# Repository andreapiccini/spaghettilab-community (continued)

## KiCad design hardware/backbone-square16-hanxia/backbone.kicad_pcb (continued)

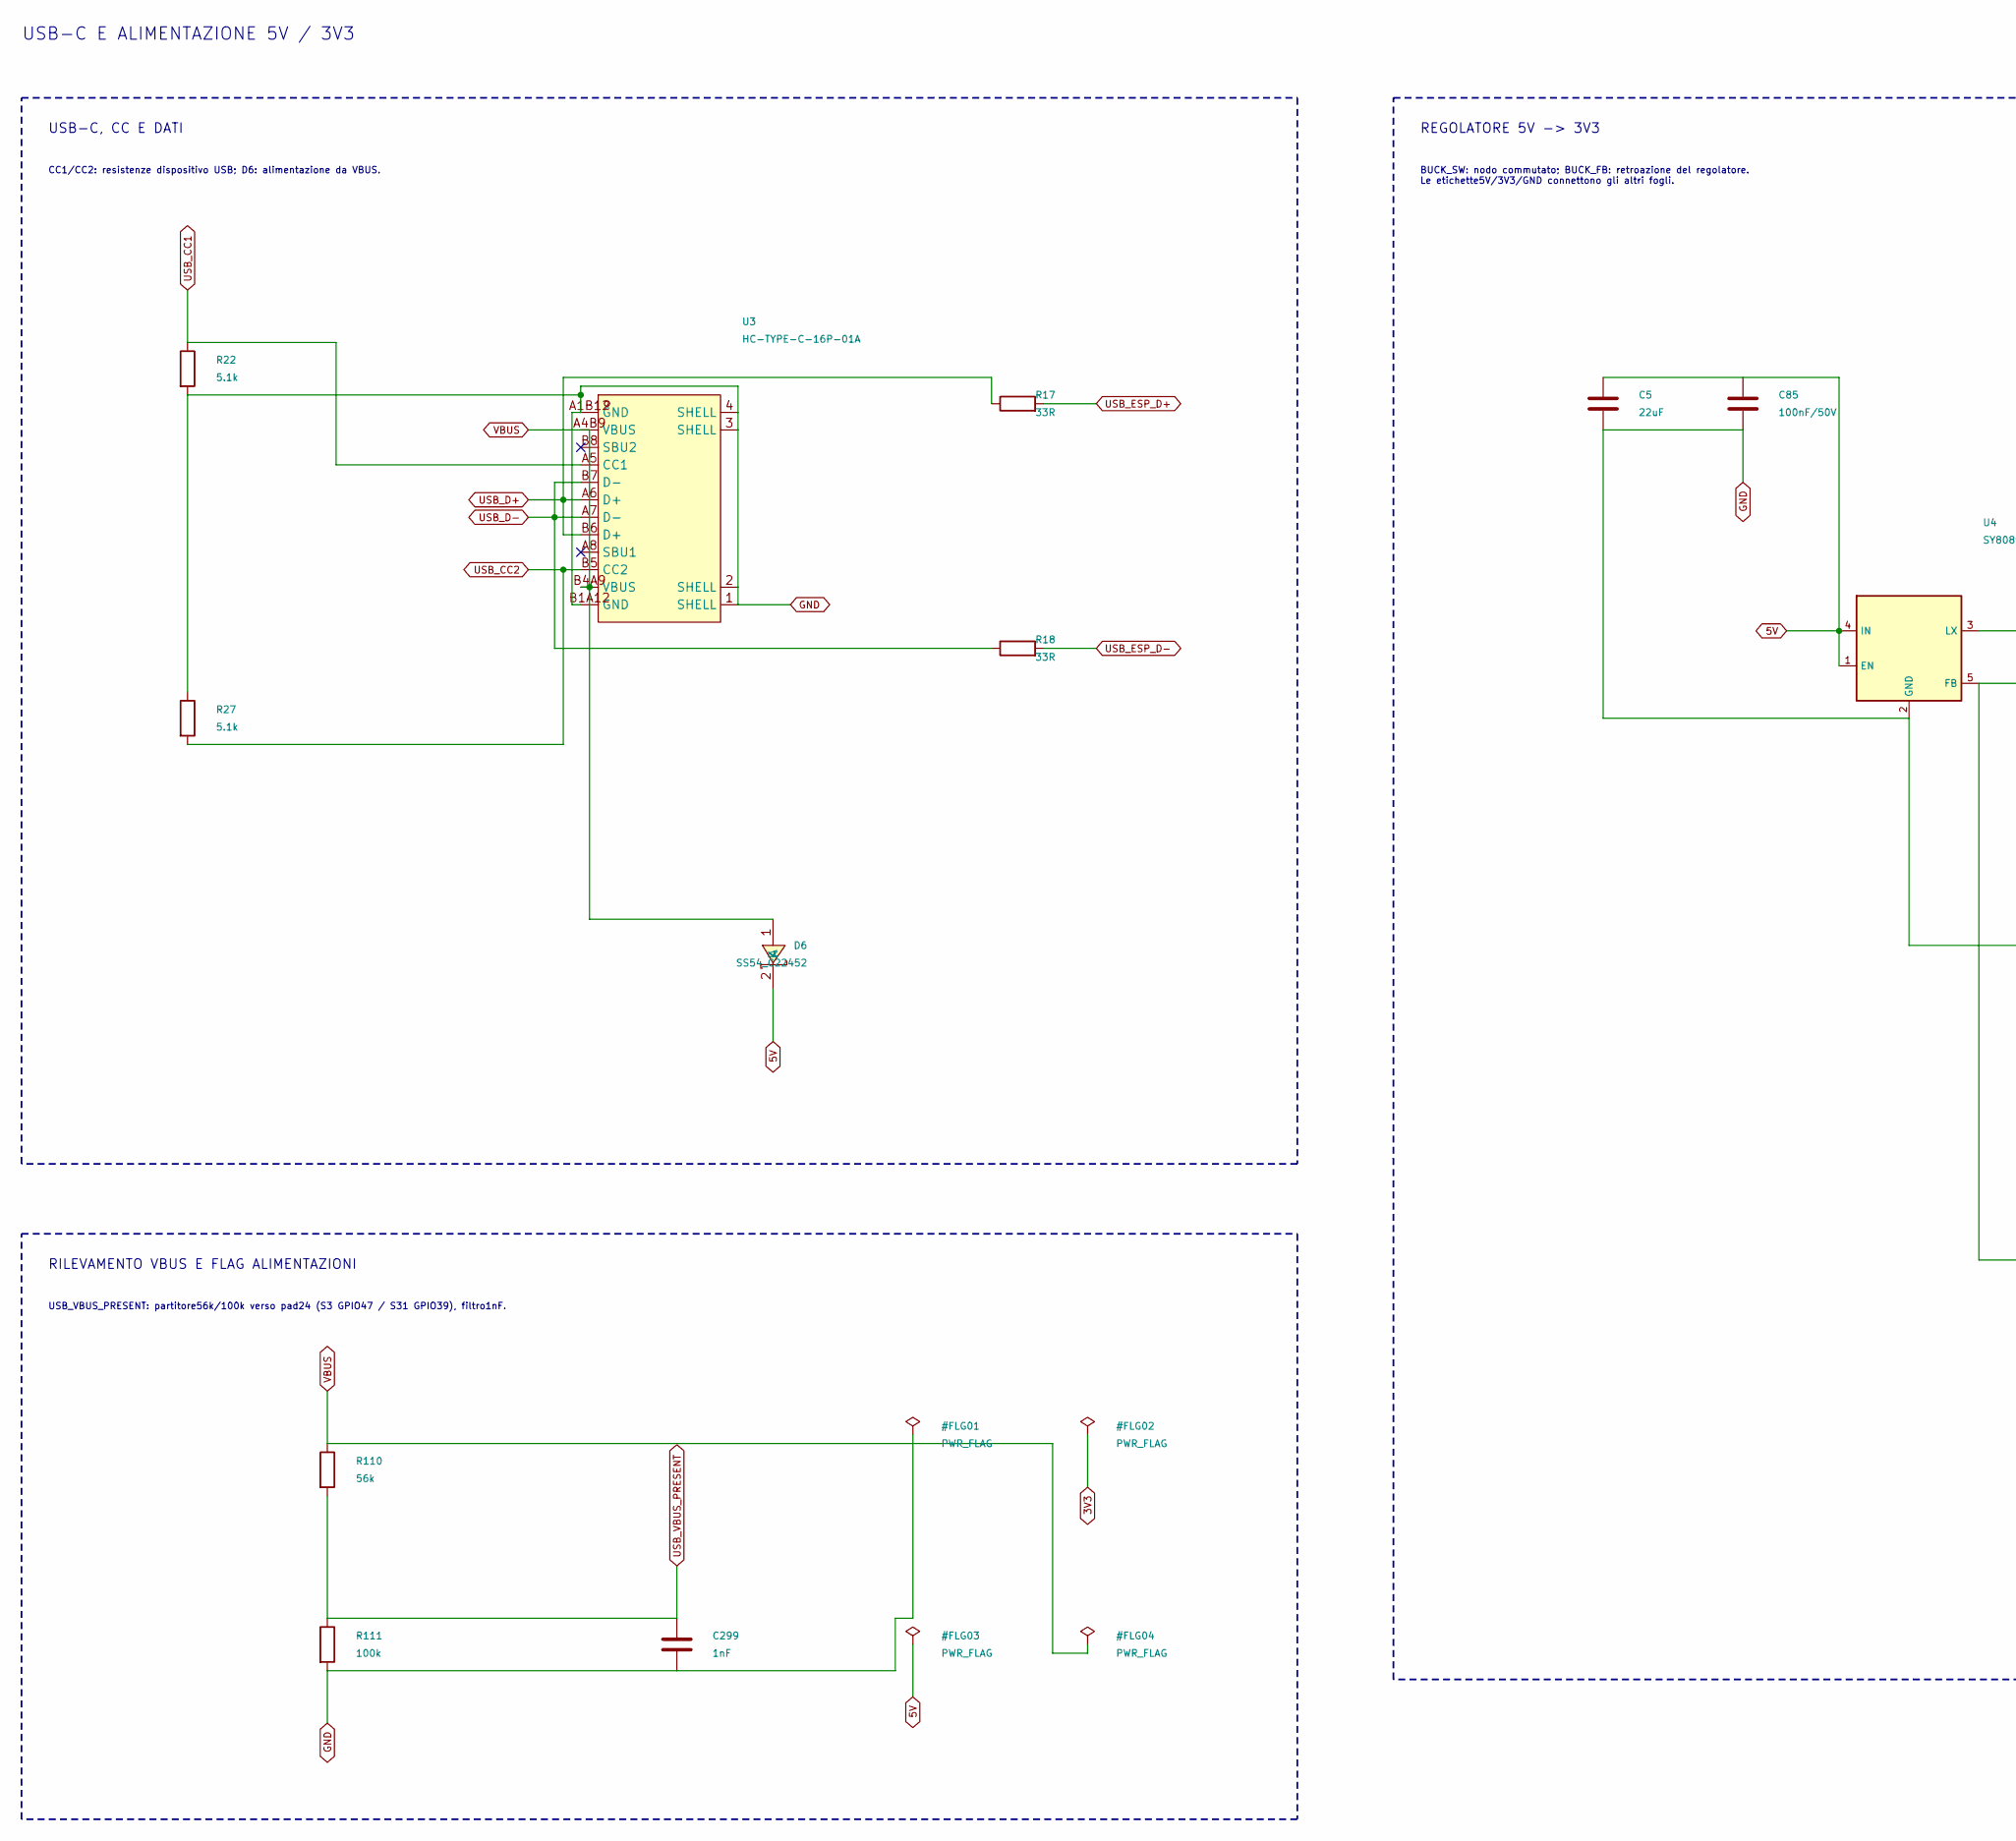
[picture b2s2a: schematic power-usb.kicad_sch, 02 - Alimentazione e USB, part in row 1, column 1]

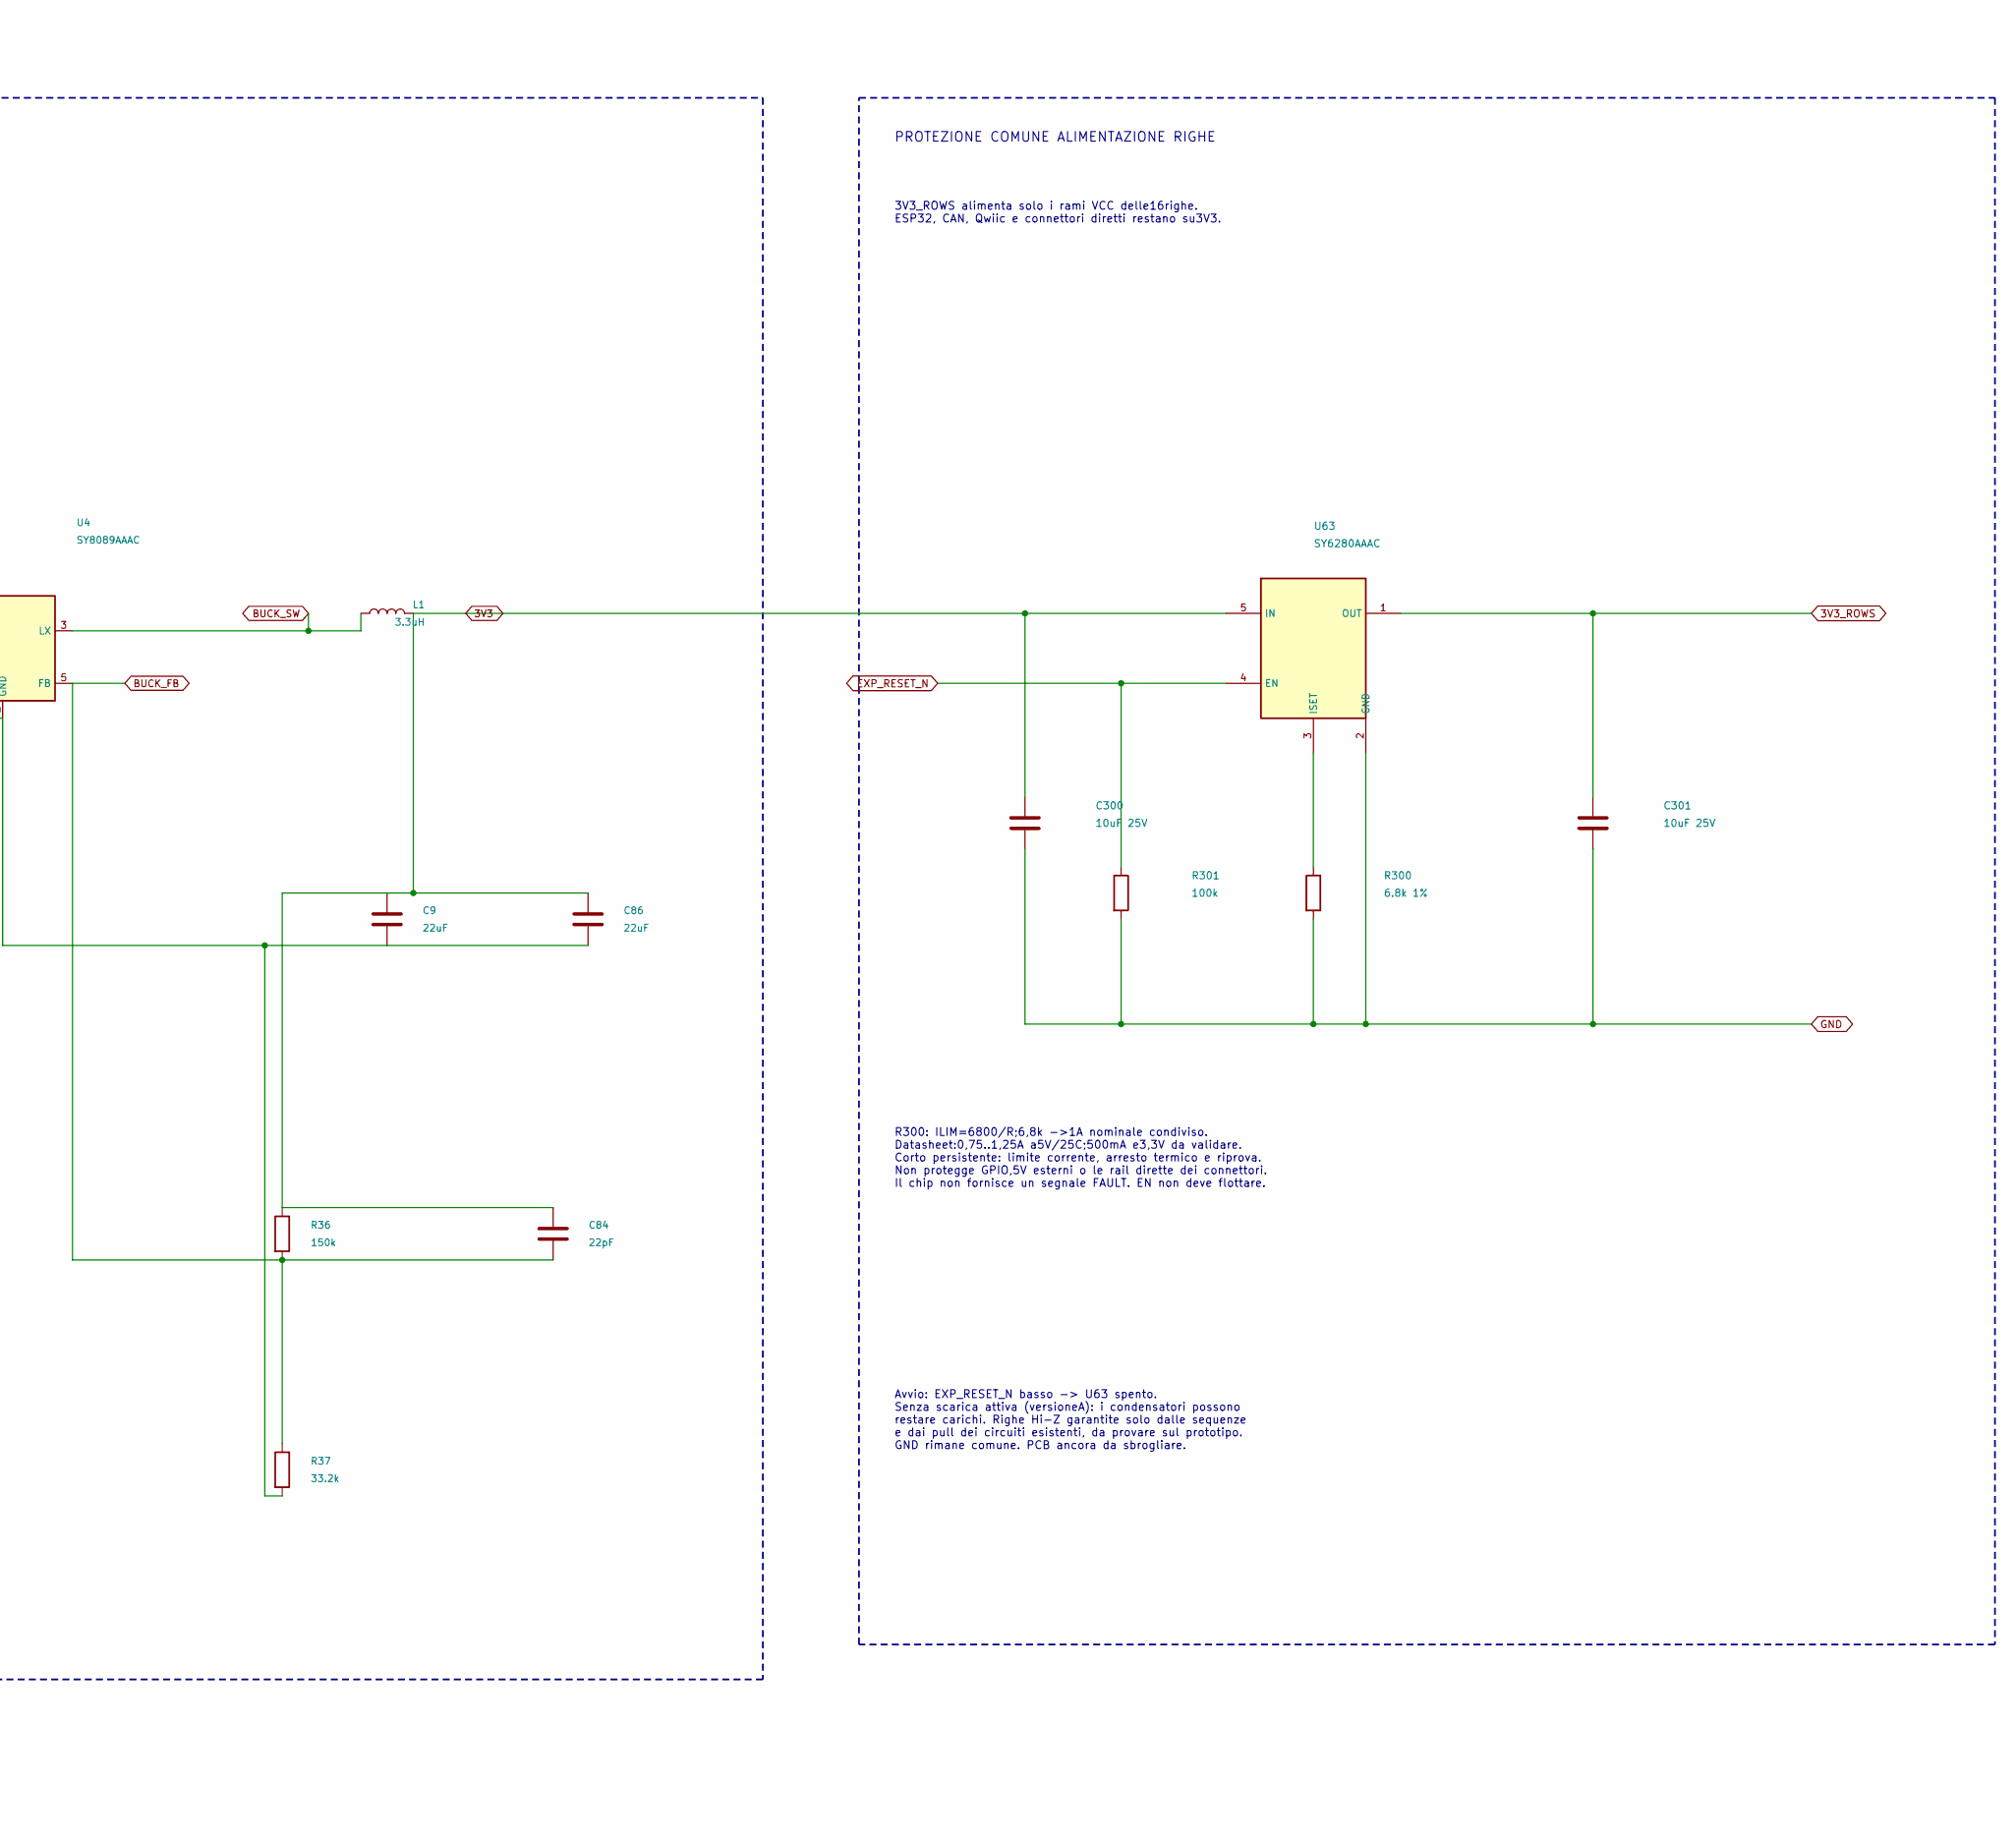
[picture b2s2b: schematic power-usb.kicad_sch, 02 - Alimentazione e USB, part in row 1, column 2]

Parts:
C5, C9, C86: 22uF; C_0603_1608Metric; MPN CL10A226MP8NUNE; LCSC Part C86295
C84: 22pF; C_0603_1608Metric; MPN CL10C220JB8NNNC; LCSC Part C1653
C85: 100nF/50V; C_0603_1608Metric; MPN CL10B104KB8NNNC; LCSC Part C1591
C299: 1nF; C_0603_1608Metric
C300, C301: 10uF 25V; C_0805_2012Metric; MPN CL21A106KAYNNNE; LCSC Part C15850
D6: SS54_C22452; SMA_L4.4-W2.8-LS5.4-R-RD; MPN SS54; LCSC Part C22452
L1: 3.3uH; L_XRTC404012S; MPN XRTC404012S3R3MBCA; LCSC Part C39846848
R17, R18: 33R; R0603; LCSC Part C2909394
R22, R27: 5.1k; R0603; LCSC Part C2907044
R36: 150k; R_0603_1608Metric; MPN 0603WAF1503T5E; LCSC Part C22807
R37: 33.2k; R_0603_1608Metric; MPN 0603WAF3322T5E; LCSC Part C23003
R110: 56k; R_0603_1608Metric
R111: 100k; R_0603_1608Metric
R300: 6.8k 1%; R_0603_1608Metric; MPN 0603WAF6801T5E; LCSC Part C23212
R301: 100k; R_0603_1608Metric; MPN 0603WAF1003T5E; LCSC Part C25803
U3: HC-TYPE-C-16P-01A; USB-C-SMD_HC-TYPE-C-16P-01A_ClearSilk; MPN HC-TYPE-C-16P-01A; LCSC Part C2894897
U4: SY8089AAAC; SOT-23-5; MPN SY8089AAAC; LCSC Part C78988
U63: SY6280AAAC; SOT-23-5; MPN SY6280AAAC; LCSC Part C207620

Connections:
3V3: C9.1, C84.1, C86.1, C300.1, L1.2, R36.1, U63.5 (IN); also elsewhere on the board
3V3_ROWS: C301.1, U63.1 (OUT); also elsewhere on the board
5V: C5.1, C85.1, D6.2 (K), U4.1 (EN), U4.4 (IN); also elsewhere on the board
BUCK_FB: C84.2, R36.2, R37.1, U4.5 (FB)
BUCK_SW: L1.1, U4.3 (LX)
EXP_RESET_N: R301.1, U63.4 (EN); also elsewhere on the board
GND: C5.2, C9.2, C85.2, C86.2, C299.2, C300.2, C301.2, R22.2, R27.1, R37.2, R111.2, R300.2, R301.2, U3.1 (SHELL), U3.2 (SHELL), U3.3 (SHELL), U3.4 (SHELL), U3.A1B12 (GND), U3.B1A12 (GND), U4.2 (GND), U63.2 (GND); also elsewhere on the board
unnamed: R300.1, U63.3 (ISET)
USB_CC1: R22.1, U3.A5 (CC1)
USB_CC2: R27.2, U3.B5 (CC2)
USB_D+: R17.1, U3.A6 (D+), U3.B6 (D+)
USB_D-: R18.1, U3.A7 (D-), U3.B7 (D-)
USB_ESP_D+: R17.2; also elsewhere on the board
USB_ESP_D-: R18.2; also elsewhere on the board
USB_VBUS_PRESENT: C299.1, R110.2, R111.1; also elsewhere on the board
VBUS: D6.1 (A), R110.1, U3.A4B9 (VBUS), U3.B4A9 (VBUS)

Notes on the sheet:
USB-C E ALIMENTAZIONE 5V / 3V3
USB-C, CC E DATI
CC1/CC2: resistenze dispositivo USB; D6: alimentazione da VBUS.
RILEVAMENTO VBUS E FLAG ALIMENTAZIONI
USB_VBUS_PRESENT: partitore56k/100k verso pad24 (S3 GPIO47 / S31 GPIO39), filtro1nF.
REGOLATORE 5V -> 3V3
BUCK_SW: nodo commutato; BUCK_FB: retroazione del regolatore. Le etichette5V/3V3/GND connettono gli altri fogli.
PROTEZIONE COMUNE ALIMENTAZIONE RIGHE
3V3_ROWS alimenta solo i rami VCC delle16righe. ESP32, CAN, Qwiic e connettori diretti restano su3V3.
R300: ILIM=6800/R;6,8k ->1A nominale condiviso. Datasheet:0,75..1,25A a5V/25C;500mA e3,3V da validare. Corto persistente: limite corrente, arresto termico e riprova. Non protegge GPIO,5V esterni o le rail dirette dei connettori. Il chip non fornisce un segnale FAULT. EN non deve flottare.
Avvio: EXP_RESET_N basso -> U63 spento. Senza scarica attiva (versioneA): i condensatori possono restare carichi. Righe Hi-Z garantite solo dalle sequenze e dai pull dei circuiti esistenti, da provare sul prototipo. GND rimane comune. PCB ancora da sbrogliare.
